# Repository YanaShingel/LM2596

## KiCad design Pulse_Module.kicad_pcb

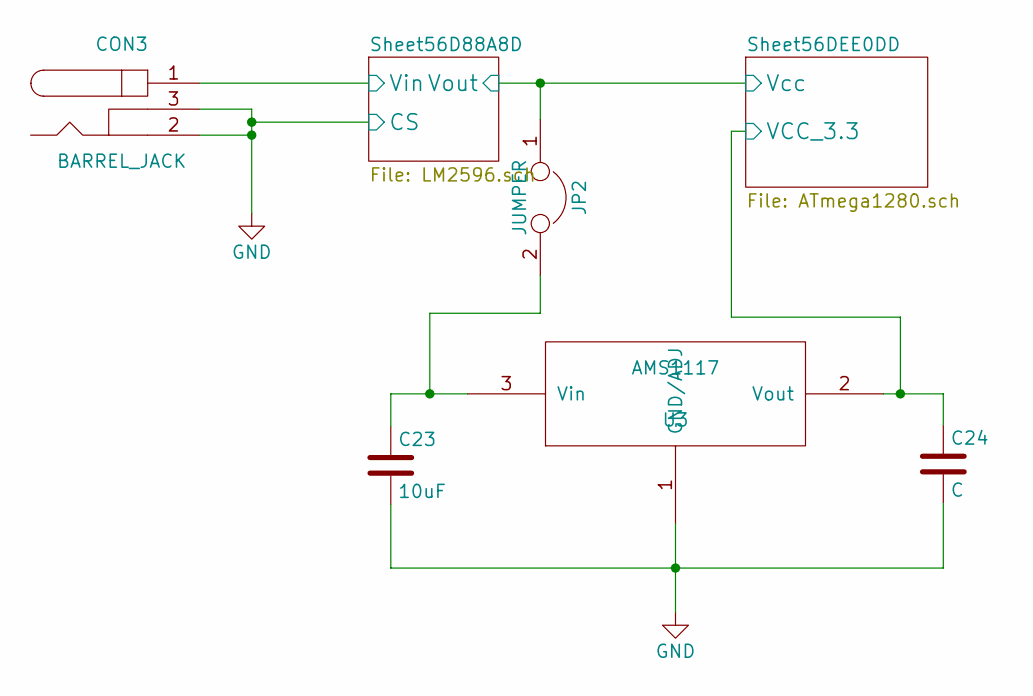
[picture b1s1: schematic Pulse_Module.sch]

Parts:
C23: 10uF; C_0805
C24: C; C_0805
CON3: BARREL_JACK
JP2: JUMPER; PINHEAD1-2
U3: AMS1117; TO-252-2Lead

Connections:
+5V: C24.1, U3.2 (Vout); also elsewhere on the board
/Sheet56D88A8D/Vin: CON3.1; also elsewhere on the board
/Sheet56DEE0DD/Vcc: JP2.1; also elsewhere on the board
unnamed: C23.1, JP2.2, U3.3 (Vin)

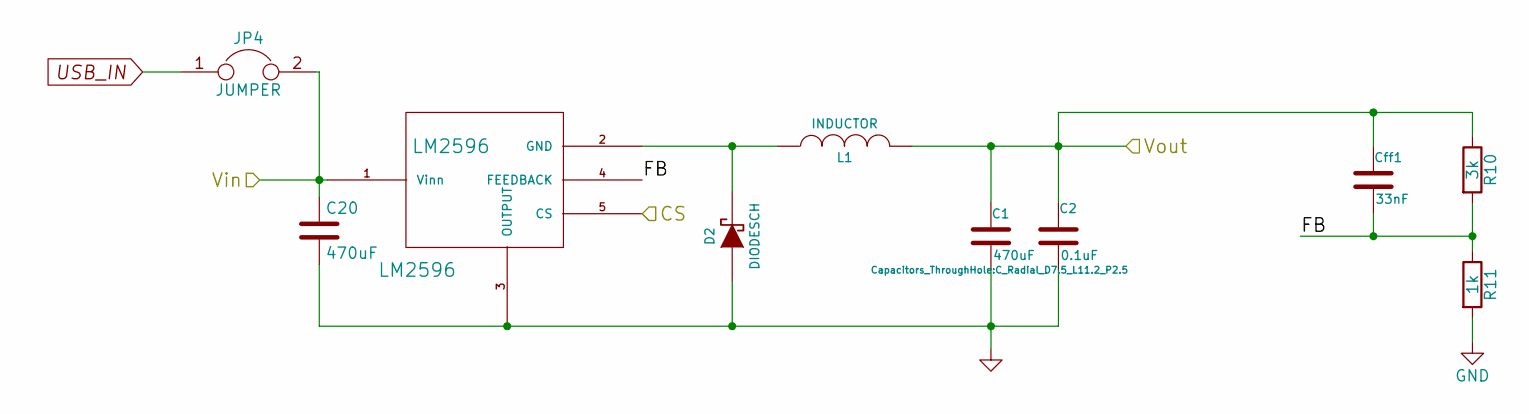
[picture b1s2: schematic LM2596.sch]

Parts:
C1, C20: 470uF; C_Radial_D7.5_L11.2_P2.5
C2: 0.1uF; C_0805
Cff1: 33nF; C_0805
D2: DIODESCH; DO-214AB
JP4: JUMPER; PINHEAD1-2
L1: INDUCTOR; INDUCTOR_12x12
LM2596: LM2596; TO-263-5Lead
R10: 3k; R_0805
R11: 1k; R_0805

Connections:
/Sheet56D88A8D/FB: Cff1.2, LM2596.4 (FEEDBACK), R10.2, R11.1; also elsewhere on the board
/Sheet56D88A8D/Vin: C20.1, JP4.2, LM2596.1 (Vinn); also elsewhere on the board
/Sheet56DEE0DD/Vcc: C1.1, C2.1, Cff1.1, L1.2, R10.1; also elsewhere on the board
unnamed: D2.2 (K), L1.1, LM2596.2 (GND)

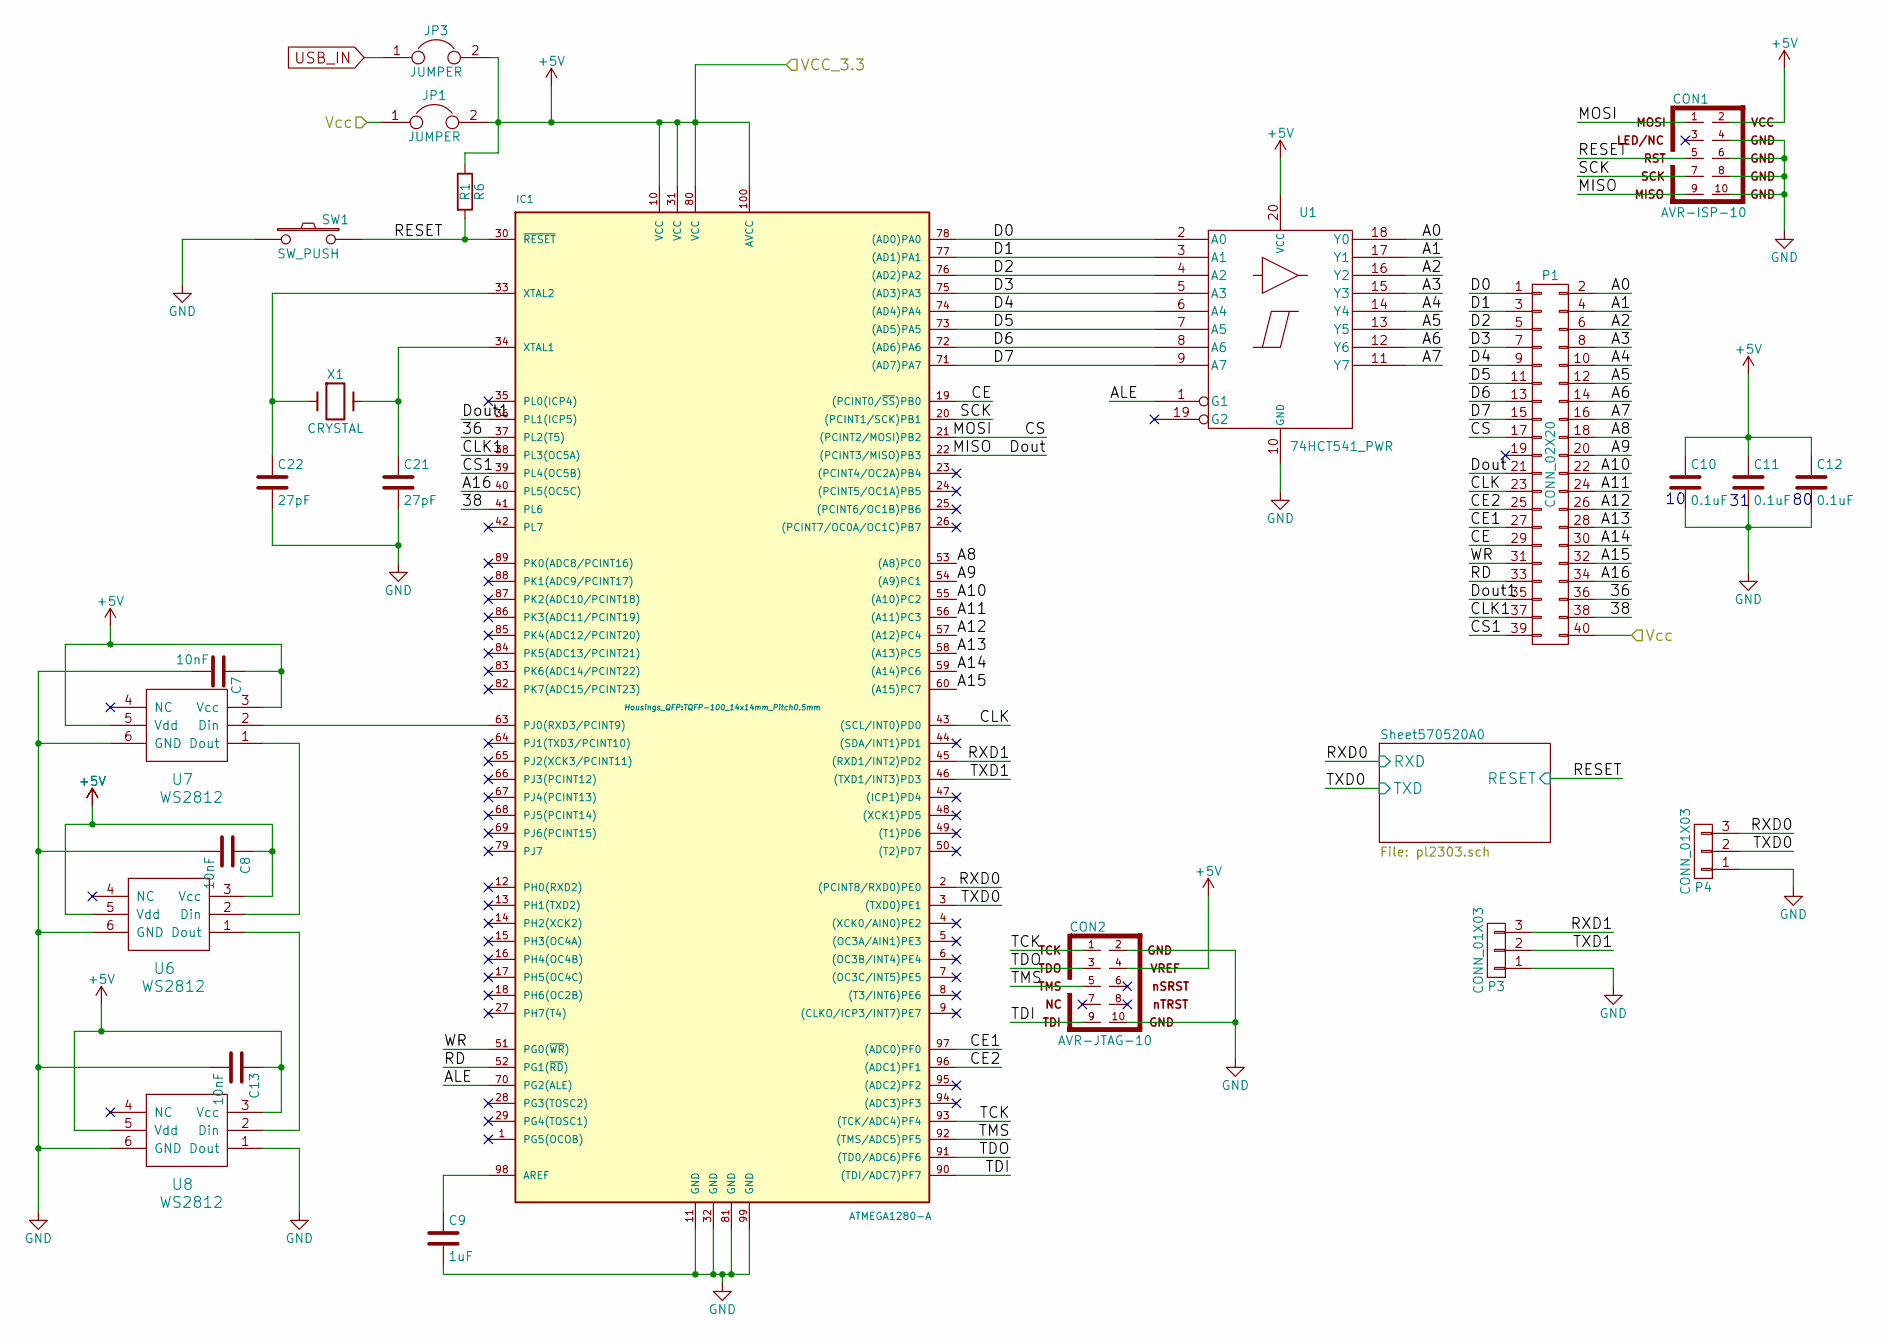
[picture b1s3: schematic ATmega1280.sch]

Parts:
C7, C8, C13: 10nF; C_0805
C9: 1uF; C_0805
C10, C11, C12: 0.1uF; C_0805
C21, C22: 27pF; C_0805
CON1: AVR-ISP-10; Pin_Header_Straight_2x05
CON2: AVR-JTAG-10; Pin_Header_Straight_2x05
IC1: ATMEGA1280-A; TQFP-100_14x14mm_Pitch0.5mm
JP1, JP3: JUMPER; PINHEAD1-2
P1: CONN_02X20; IDC_Header_Straight_40pins
P3, P4: CONN_01X03; Pin_Header_Angled_1x03
R6: R1; R_0805
SW1: SW_PUSH; SW_PUSH_SMALL
U1: 74HCT541_PWR; SSOP-20_5.3x7.2mm_Pitch0.65mm
U6, U7, U8: WS2812; 5050
X1: CRYSTAL; Crystal_HC49-U_Vertical

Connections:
+5V: C7.1, C8.1, C10.1, C11.1, C12.1, C13.1, CON1.2, CON2.4, IC1.10 (VCC), IC1.31 (VCC), IC1.80 (VCC), IC1.100 (AVCC), JP1.2, JP3.2, R6.1, U1.20 (VCC), U6.3 (Vcc), U6.5 (Vdd), U7.3 (Vcc), U7.5 (Vdd), U8.3 (Vcc), U8.5 (Vdd); also elsewhere on the board
/Sheet56DEE0DD/36: IC1.37 (PL2(T5)), P1.36
/Sheet56DEE0DD/38: IC1.41 (PL6), P1.38
/Sheet56DEE0DD/A0: P1.2, U1.18 (Y0)
/Sheet56DEE0DD/A1: P1.4, U1.17 (Y1)
/Sheet56DEE0DD/A2: P1.6, U1.16 (Y2)
/Sheet56DEE0DD/A3: P1.8, U1.15 (Y3)
/Sheet56DEE0DD/A4: P1.10, U1.14 (Y4)
/Sheet56DEE0DD/A5: P1.12, U1.13 (Y5)
/Sheet56DEE0DD/A6: P1.14, U1.12 (Y6)
/Sheet56DEE0DD/A7: P1.16, U1.11 (Y7)
/Sheet56DEE0DD/A8: IC1.53 ((A8)PC0), P1.18
/Sheet56DEE0DD/A9: IC1.54 ((A9)PC1), P1.20
/Sheet56DEE0DD/A10: IC1.55 ((A10)PC2), P1.22
/Sheet56DEE0DD/A11: IC1.56 ((A11)PC3), P1.24
/Sheet56DEE0DD/A12: IC1.57 ((A12)PC4), P1.26
/Sheet56DEE0DD/A13: IC1.58 ((A13)PC5), P1.28
/Sheet56DEE0DD/A14: IC1.59 ((A14)PC6), P1.30
/Sheet56DEE0DD/A15: IC1.60 ((A15)PC7), P1.32
/Sheet56DEE0DD/ALE: IC1.70 (PG2(ALE)), U1.1 (G1)
/Sheet56DEE0DD/CE: IC1.19 ((PCINT0/~SS~)PB0), P1.29
/Sheet56DEE0DD/CE1: IC1.97 ((ADC0)PF0), P1.27
/Sheet56DEE0DD/CE2: IC1.96 ((ADC1)PF1), P1.25
/Sheet56DEE0DD/CLK: IC1.43 ((SCL/INT0)PD0), P1.23
/Sheet56DEE0DD/CLK1: IC1.38 (PL3(OC5A)), P1.37
/Sheet56DEE0DD/CS: CON1.1, IC1.21 ((PCINT2/MOSI)PB2), P1.17
/Sheet56DEE0DD/CS1: IC1.39 (PL4(OC5B)), P1.39
/Sheet56DEE0DD/D0: IC1.78 ((AD0)PA0), P1.1, U1.2 (A0)
/Sheet56DEE0DD/D1: IC1.77 ((AD1)PA1), P1.3, U1.3 (A1)
/Sheet56DEE0DD/D2: IC1.76 ((AD2)PA2), P1.5, U1.4 (A2)
/Sheet56DEE0DD/D3: IC1.75 ((AD3)PA3), P1.7, U1.5 (A3)
/Sheet56DEE0DD/D4: IC1.74 ((AD4)PA4), P1.9, U1.6 (A4)
/Sheet56DEE0DD/D5: IC1.73 ((AD5)PA5), P1.11, U1.7 (A5)
/Sheet56DEE0DD/D6: IC1.72 ((AD6)PA6), P1.13, U1.8 (A6)
/Sheet56DEE0DD/D7: IC1.71 ((AD7)PA7), P1.15, U1.9 (A7)
/Sheet56DEE0DD/Dout: CON1.9, IC1.22 ((PCINT3/MISO)PB3), P1.21
/Sheet56DEE0DD/Dout1: IC1.36 (PL1(ICP5)), P1.35
/Sheet56DEE0DD/RD: IC1.52 (PG1(~RD~)), P1.33
/Sheet56DEE0DD/RXD1: IC1.45 ((RXD1/INT2)PD2), P3.3
/Sheet56DEE0DD/SCK: CON1.7, IC1.20 ((PCINT1/SCK)PB1)
/Sheet56DEE0DD/Sheet570520A0/RESET: CON1.5, IC1.30 (~RESET), R6.2, SW1.2; also elsewhere on the board
/Sheet56DEE0DD/Sheet570520A0/RXD: IC1.2 ((PCINT8/RXD0)PE0), P4.3; also elsewhere on the board
/Sheet56DEE0DD/Sheet570520A0/TXD: IC1.3 ((TXD0)PE1), P4.2; also elsewhere on the board
/Sheet56DEE0DD/TCK: CON2.1, IC1.93 ((TCK/ADC4)PF4)
/Sheet56DEE0DD/TDI: CON2.9, IC1.90 ((TDI/ADC7)PF7)
/Sheet56DEE0DD/TDO: CON2.3, IC1.91 ((TD0/ADC6)PF6)
/Sheet56DEE0DD/TMS: CON2.5, IC1.92 ((TMS/ADC5)PF5)
/Sheet56DEE0DD/TXD1: IC1.46 ((TXD1/INT3)PD3), P3.2
/Sheet56DEE0DD/Vcc: JP1.1, P1.40; also elsewhere on the board
/Sheet56DEE0DD/WR: IC1.51 (PG0(~WR~)), P1.31
/Sheet56DEE0DD/А16: IC1.40 (PL5(OC5C)), P1.34
unnamed: C9.1, IC1.98 (AREF)
unnamed: C21.1, IC1.34 (XTAL1), X1.2
unnamed: C22.1, IC1.33 (XTAL2), X1.1
unnamed: IC1.63 (PJ0(RXD3/PCINT9)), U7.2 (Din)
unnamed: U6.1 (Dout), U8.2 (Din)
unnamed: U6.2 (Din), U7.1 (Dout)

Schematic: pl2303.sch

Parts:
C3, C5, C6, C14, C15, C16, C18: 0.1uF; C_0805
C4, C19: 27pF; C_0805
C17: 0.1U; C_0805
D1: LED_TX; LED_0805
D3: LED_RX; LED_0805
P2: USB_OTG; USB_Micro-B
R1, R7: 220-470; R_0805
R2, R8: 220; R_0805
R3, R4: 27; R_0805
R5: 1.5K; R_0805
R12, R13: 470; R_0805
U2: PL2303; SSOP-28_5.3x10.2mm_Pitch0.65mm
Y1: CRYSTAL; Crystal_HC49-U_Vertical

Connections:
+3V3: C15.1, C17.1, C18.1, R5.2, U2.17 (VDD_3V3)
+5V: C3.2, C5.2, C6.2, C16.1, R8.2, U2.4 (VDD_232); also elsewhere on the board
/Sheet56DEE0DD/Sheet570520A0/D+: R4.1, U2.15 (DP)
/Sheet56DEE0DD/Sheet570520A0/D-: R3.1, U2.16 (DM)
/Sheet56DEE0DD/Sheet570520A0/RESET: C14.2, U2.19 (RESET); also elsewhere on the board
/Sheet56DEE0DD/Sheet570520A0/RXD: D3.2 (A), R13.1; also elsewhere on the board
/Sheet56DEE0DD/Sheet570520A0/TXD: D1.2 (A), R12.1; also elsewhere on the board
unnamed: C4.1, U2.28 (OSC2), Y1.1
unnamed: C14.1, U2.2 (DTR_N)
unnamed: C19.1, U2.27 (OSC1), Y1.2
unnamed: D1.1 (K), R1.1
unnamed: D3.1 (K), R7.1
unnamed: P2.2 (D-), R3.2
unnamed: P2.3 (D+), R4.2, R5.1
unnamed: R2.1, U2.23 (LD_MODE)
unnamed: R8.1, U2.22 (TRI_MODE)
unnamed: R12.2, U2.1 (TXD)
unnamed: R13.2, U2.5 (RXD)

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
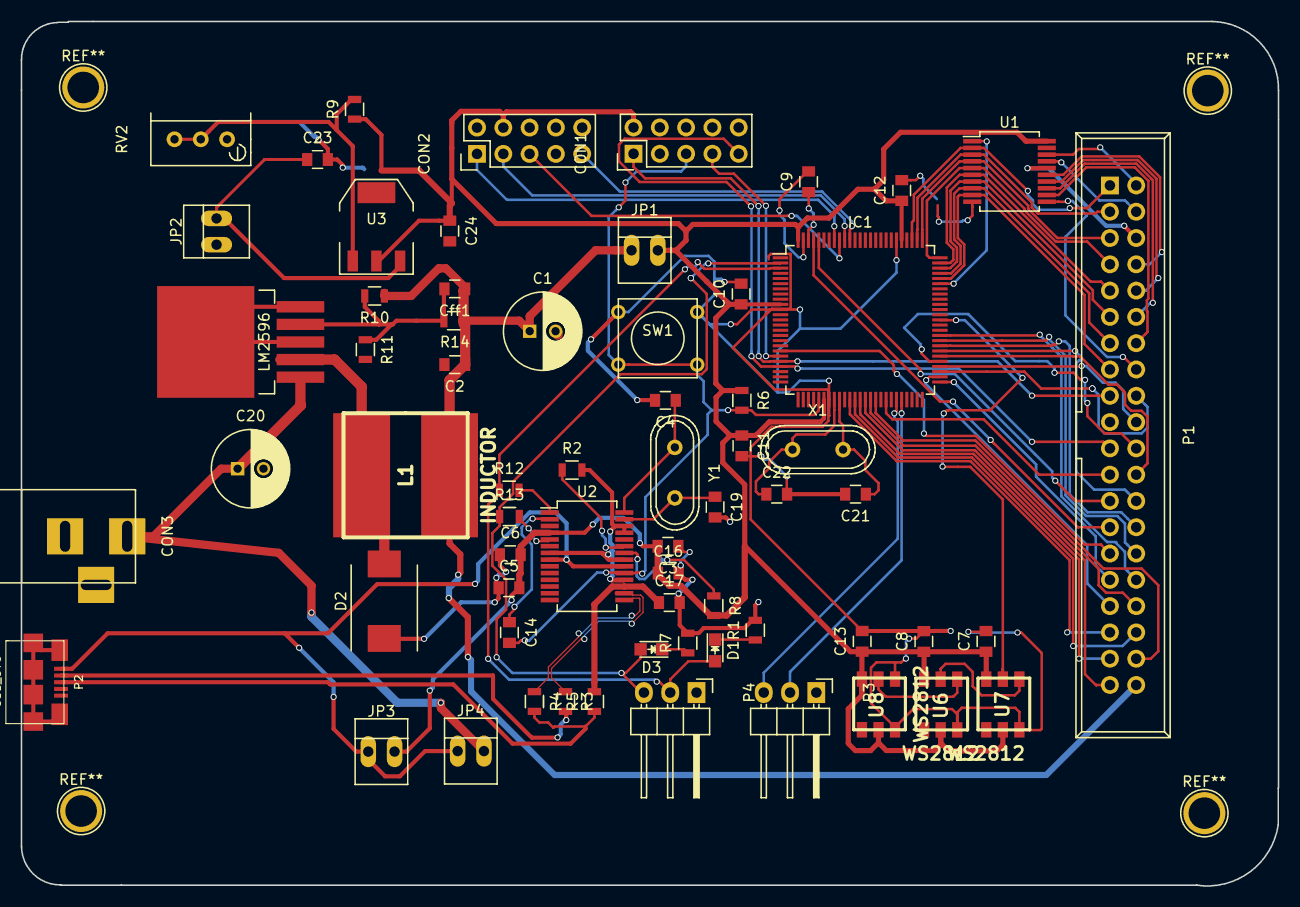
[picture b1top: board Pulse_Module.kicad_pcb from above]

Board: 2 copper layers, 121.4 x 83.5 mm, 64 parts (0 on the bottom side), 78 nets.

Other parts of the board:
R9: R; R_0805
R14: 1k; R_0805
RV2: POT; Potentiometer_Bourns_3296W_3-8Zoll_Inline_ScrewUp

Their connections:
+5V: R9.1; also elsewhere on the board
/Sheet56D88A8D/FB: R14.2; also elsewhere on the board
/Sheet56DEE0DD/Vcc: R14.1; also elsewhere on the board

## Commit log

2016-03-14 Подключены программатор, питание и генератор
2016-03-14 небольшие изменения
2016-04-07 Добавление 40пинового разъёма и UART
2016-04-12 Исправлено согласно комментариям
2016-04-13 исправление аннотации
2016-04-16 Аннотированные элементы
2016-04-20 исправление ошибок
2016-04-25 Добавление WS2812, исправление всех замечаний
2016-04-27 Добавлен JTAG и SPI
2016-05-05 Изменения в CvPCB
2016-05-05 Небольшие изменения в Pcbnew
2016-05-16 Изменения футпринтов и расположения на плате
2016-05-16 разводка питания
2016-05-17 Разведено LM2596
2016-05-21 Питание и LM2596
2016-05-21 исправления
2016-05-22 LM2596
2016-05-26 исправлена LM2596
2016-06-06 Готовая плата версия_1
2016-06-06 Переразведённая лмка
2016-06-19 исправление согласно замечаниям, переразведена PL2303
2016-07-05 подключение питания LMки от USB
2016-07-19 разделение питания и добавление потенциометра у лмки
2016-10-03 Добавлен AMS1117 и изменения в питании
2016-10-04 Выбор футпринта для LMS1117
2016-10-06 Изменения футпринтов
2016-10-09 Последние изменения
2016-10-09 Последние изменения на плате
2016-10-20 перенесён футпринт С1 вперёд
2016-10-31 изменён футпринт usb и амс
2017-02-09 Точно последняя версия
